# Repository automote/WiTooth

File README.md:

# WiTooth

The WiTooth is based on Espressif ESP32 WiFi-BT-BLE SoC (System on Chip), ESP32 contains two low-power Xtensa® 32-bit LX6 microprocessors running at 80 MHz. Features include:

 * Integrated 802.11 BGN WiFi transceiver
 * Integrated dual-mode Bluetooth (classic and BLE)
 * Dual-core Tensilica LX6 microprocessor
 * Up to 240MHz clock frequency
 * 520kB internal SRAM
 * 10-electrode capacitive touch support
 * Hardware accelerated encryption (AES, SHA2, ECC, RSA-4096)
 * 2.2 to 3.6V operating range
 * 2.5 µA deep sleep current
 * 3 SPI, 2 I2C, 2 UART
 * 16 PWM outputs
 * 2 DAC
 * 2 I2S
 * 18 analog-to-digital converter (ADC) channels
 
## Platform Features

 * Compatible with Arduino IDE
 * USB powered
 * CP2102 USB-to-UART Bridge
 * Extended breadboard compatible headers
 * UART, SPI, I2C
 * On-board RESET

## Changelog
 - v1.1
	+ Grounding via added
	+ Version bumped to 1.1
 - v1.0
	+ Updated 2N3904 symbol and footprint
	+ removed JTAG headers
 
## Maintainers

The WiTooth is maintained by thingTronics Innovations.

Main contributor:
 * Manohar Bompella @<manohar.bompella@thingtronics.com>
 * Poornima Nagesh @<poornima.nagesh@thingtronics.com>
 * Lovelesh Patel @<lovelesh.patel@thingtronics.com>

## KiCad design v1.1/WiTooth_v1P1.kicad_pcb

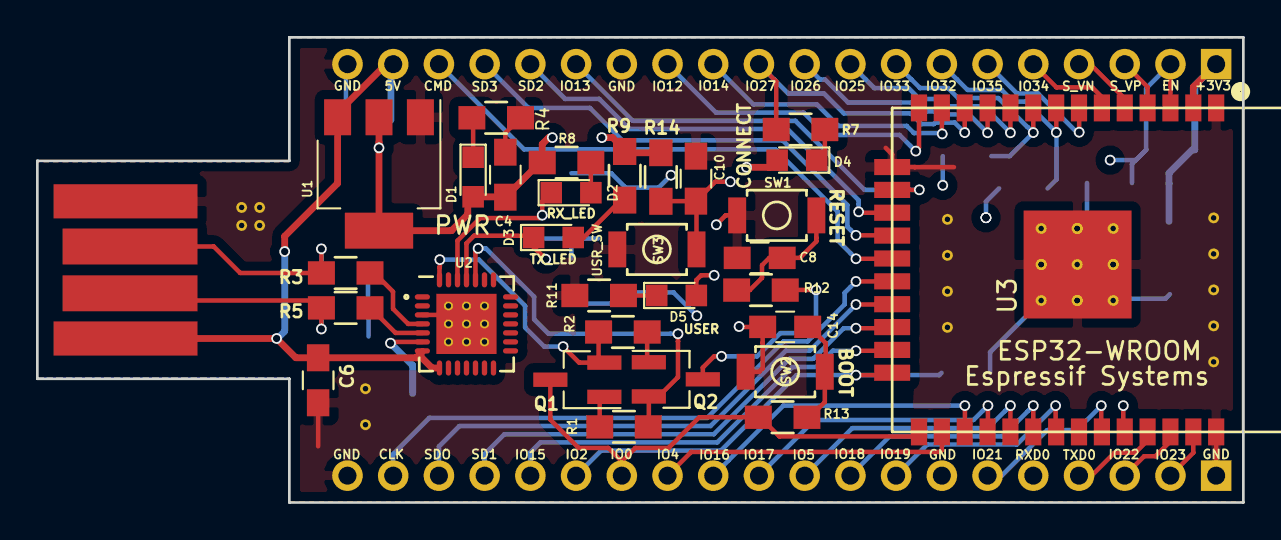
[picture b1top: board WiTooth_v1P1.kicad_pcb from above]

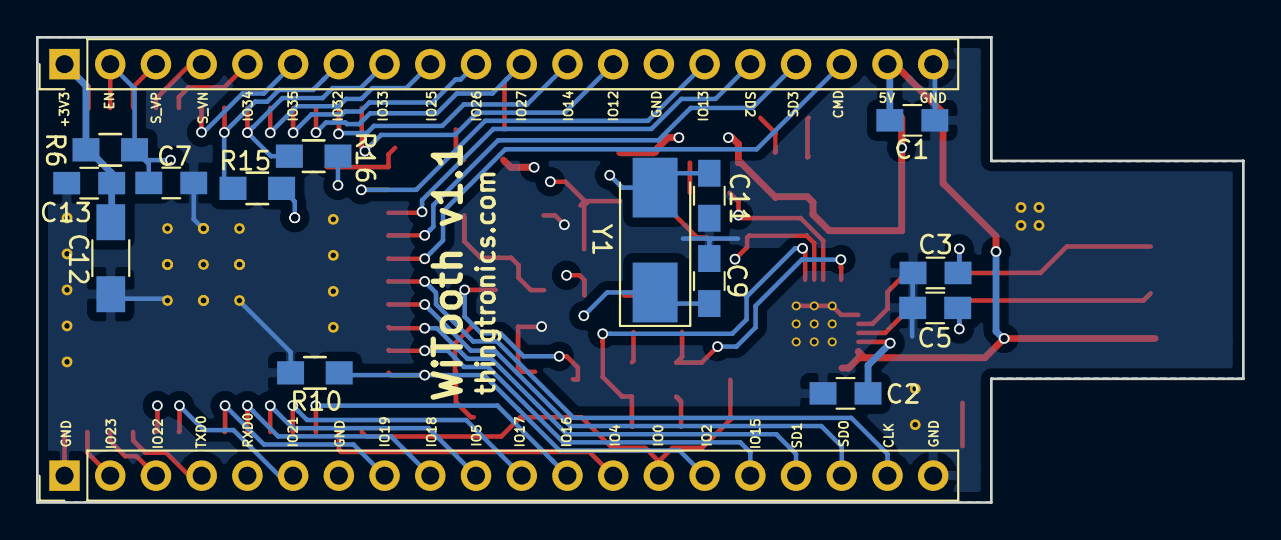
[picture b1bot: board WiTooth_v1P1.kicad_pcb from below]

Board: 4 copper layers, 67.0 x 25.8 mm, 47 parts (16 on the bottom side), 54 nets.

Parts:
C1, C4: 10uF; C_0805_HandSoldering
C2: 0.1uF; C_0805_HandSoldering
C3, C5: 47pF; C_0805_HandSoldering
C6, C13: 1uF; C_0805_HandSoldering
C7, C8, C10, C14: 1nF; C_0805_HandSoldering
C9, C11: 27pF; C_0805_HandSoldering
C12: 100uF; C_1206_HandSoldering
D1: PWR; LED_0805
D2: RX_LED; LED_0805
D3: TX_LED; LED_0805
D4: CONNECT; LED_0805
D5: USER; LED_0805
P1: USB_A_MALE; usb-PCB_male
P4, P5: CONN_01X20; Pin_Header_Straight_1x20_Pitch2.54mm
Q1, Q2: MMBT3904; SOT-23_Handsoldering
R1, R2, R6: 12K; R_0805_HandSoldering
R3, R5: 27E; R_0805_HandSoldering
R4, R8, R9: 1K; R_0805_HandSoldering
R7, R11, R12, R13, R14: 470E; R_0805_HandSoldering
R10: 5K; R_0805_HandSoldering
R15, R16: 0E; R_0805_HandSoldering
SW1: RESET; SW_SPST_B3U-1000P_SUNROM
SW2: BOOT; SW_SPST_B3U-1000P_SUNROM
SW3: USER_SW; SW_SPST_B3U-1000P_SUNROM
U1: AMS1117-3V3; SOT-223
U2: CP2102; QFN-28-1EP_5x5mm_Pitch0.5mm
U3: ESP-32_WROOM32_Rectangle; ESP32-WROOM_SMALLER_FOOTPRINT
Y1: Crystal; Crystal_SMD_0603-2pin_6.0x3.5mm_HandSoldering

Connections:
+3V3: C4.1, C12.1, C13.1, D1.2, D4.2, P4.1, R6.1, R8.1, R9.1, R14.1, U1.2, U1.4, U3.2
+5V: C1.1, C6.1, P1.1, P4.19, U1.3, U2.7, U2.8
CLK: P5.19, U3.20
CMD: P4.18, U3.19
DTR: Q1.2, R2.2, U2.28
EN: C7.1, P4.2, Q2.3, R6.2, R12.1, U3.3
GND: C1.2, C2.2, C3.2, C4.2, C5.2, C6.2, C7.2, C8.2, C9.2, C10.2, C11.2, C12.2, C13.2, C14.2, P1.4, P4.14, P4.20, P5.1, P5.7, P5.20, R4.2, R10.2, R11.2, SW1.1, SW2.1, SW3.1, U1.1, U2.3, U2.29, U3.1, U3.15, U3.38, U3.39
IO0: P5.14, Q1.3, R13.1, U3.25
IO2: P5.15, R10.1, U3.24
IO4: P5.13, U3.26
IO5: P5.10, U3.29
IO12: P4.13, U3.14
IO13: P4.15, U3.16
IO14: P4.12, U3.13
IO15: P5.16, U3.23
IO16: P5.12, U3.27
IO17: P5.11, U3.28
IO18: P5.9, U3.30
IO19: P5.8, U3.31
IO21: P5.6, U3.33
IO22: P5.3, U3.36
IO23: P5.2, U3.37
IO25: P4.9, U3.10
IO26: P4.10, U3.11
IO27: P4.11, R7.2, U3.12
IO32: P4.7, R15.1, U3.8
IO33: P4.8, R16.1, U3.9
IO34: C10.1, P4.5, R14.2, SW3.2, U3.6
IO35: D5.2, P4.6, U3.7
unnamed: C3.1, P1.3, R3.2
unnamed: C5.1, P1.2, R5.2
unnamed: C8.1, R12.2, SW1.2
unnamed: C9.1, R15.2, Y1.1
unnamed: C11.1, R16.2, Y1.2
unnamed: C14.1, R13.2, SW2.2
unnamed: D1.1, R4.1
unnamed: D2.2, R8.2
unnamed: D3.2, R9.2
unnamed: D4.1, R7.1
unnamed: D5.1, R11.1
unnamed: Q1.1, R1.1
unnamed: Q2.1, R2.1
unnamed: R3.1, U2.4
unnamed: R5.1, U2.5
RTS: Q2.2, R1.2, U2.24
RXD0: D2.1, P5.5, U2.26, U3.34
SD0: P5.18, U3.21
SD1: P5.17, U3.22
SD2: P4.16, U3.17
SD3: P4.17, U3.18
SENSOR_VN: P4.4, U3.5
SENSOR_VP: P4.3, U3.4
TXD0: D3.1, P5.4, U2.25, U3.35
VDD: C2.1, U2.6

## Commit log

2017-02-17 Added images folder; schematic verified
2017-02-18 verified layout; ready for fab
2017-02-18 BOM verified
2017-02-22 updated the 2N3904 npn transistor footprint
2017-02-23 minor changes to DWGS.User file
2017-03-06 bumped up the project to v1.1; added extra grounding in layout
2017-03-24 updated README with changelog
